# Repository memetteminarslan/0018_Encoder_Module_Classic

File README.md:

# 0018_Encoder_Module_Classic
You are seeing a large number of widely used Encoder modules in electronic development kits. More information coming soon...

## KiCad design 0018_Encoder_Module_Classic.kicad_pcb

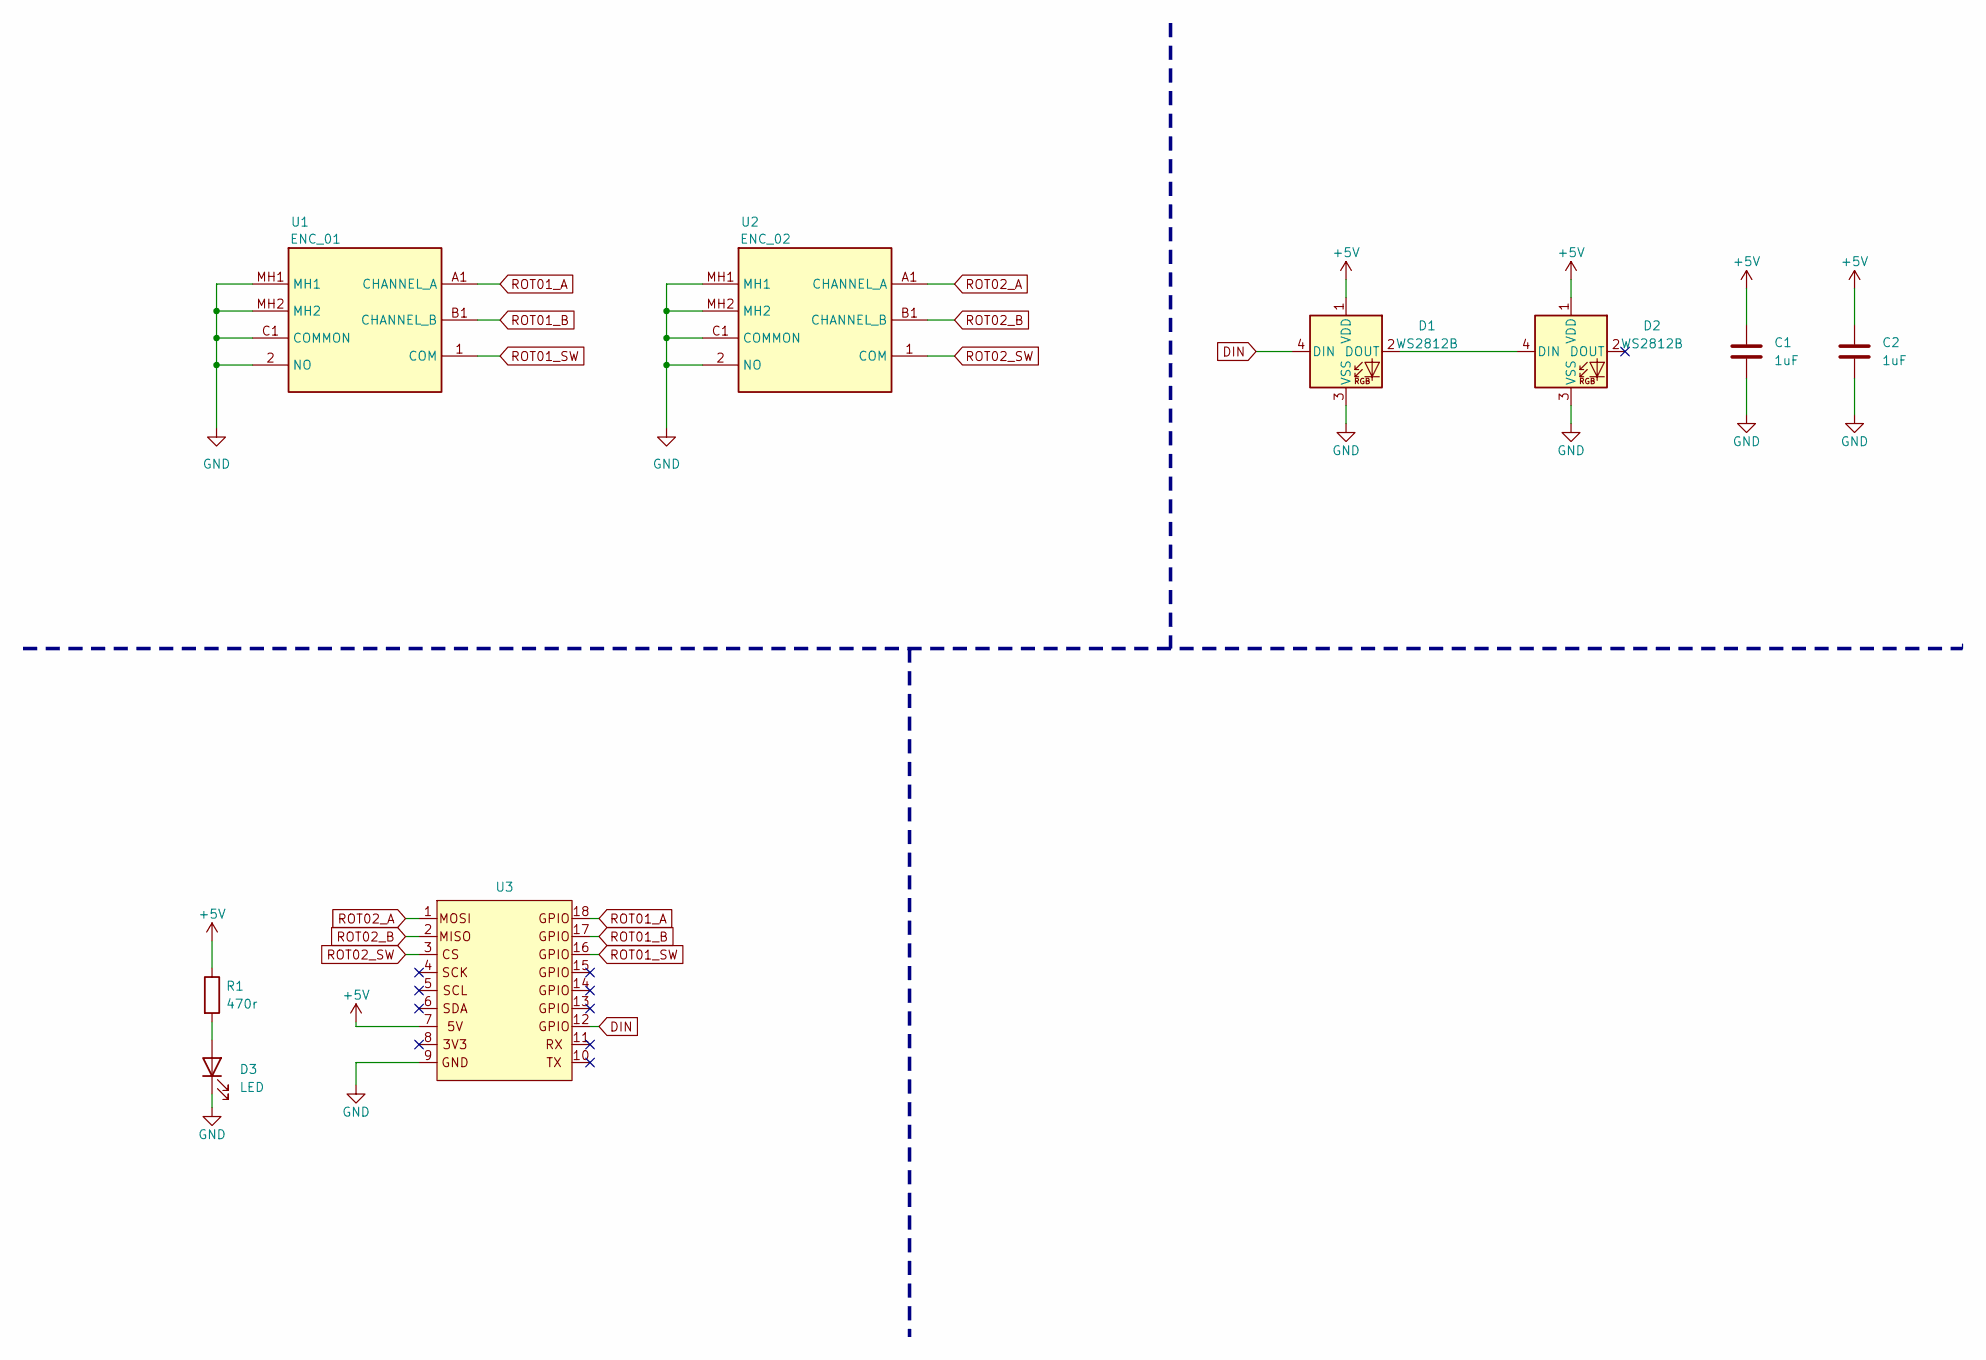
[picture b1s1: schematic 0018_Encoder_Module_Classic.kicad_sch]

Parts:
C1, C2: 1uF; C_0603_1608Metric
D1, D2: WS2812B; LED_WS2812B_PLCC4_5.0x5.0mm_P3.2mm
D3: LED; LED_0603_1608Metric
R1: 470r; R_0603_1608Metric
U1: ENC_01; PEC11R4215FS0024; Mouser Part Number 652-PEC11R-4215F-S24
U2: ENC_02; PEC11R4215FS0024; Mouser Part Number 652-PEC11R-4215F-S24
U3: pin_header_5-3

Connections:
+5V: C1.1, C2.1, D1.1 (VDD), D2.1 (VDD), R1.1, U3.7
DIN: D1.4 (DIN), U3.12
GND: C1.2, C2.2, D1.3 (VSS), D2.3 (VSS), D3.1 (K), U1.2 (NO), U1.C1 (COMMON), U1.MH1, U1.MH2, U2.2 (NO), U2.C1 (COMMON), U2.MH1, U2.MH2, U3.9
unnamed: D1.2 (DOUT), D2.4 (DIN)
unnamed: D3.2 (A), R1.2
ROT01_A: U1.A1 (CHANNEL_A), U3.18
ROT01_B: U1.B1 (CHANNEL_B), U3.17
ROT01_SW: U1.1 (COM), U3.16
ROT02_A: U2.A1 (CHANNEL_A), U3.1
ROT02_B: U2.B1 (CHANNEL_B), U3.2
ROT02_SW: U2.1 (COM), U3.3

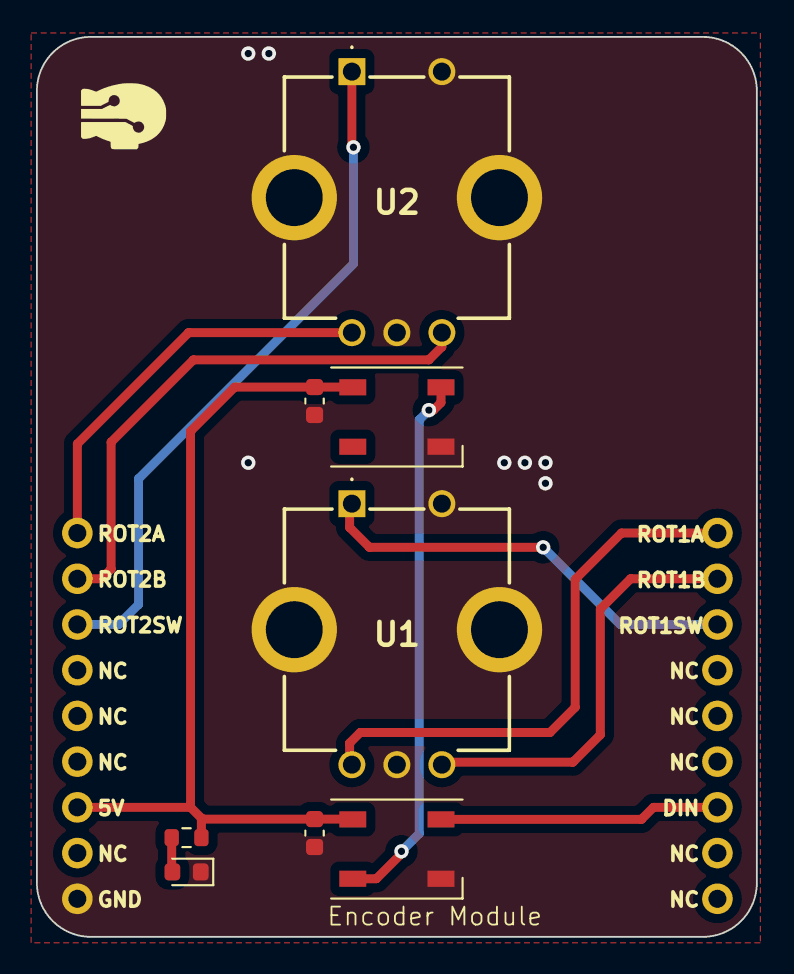
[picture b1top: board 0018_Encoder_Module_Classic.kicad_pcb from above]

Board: 2 copper layers, 40.0 x 50.0 mm, 9 parts (0 on the bottom side), 11 nets.
